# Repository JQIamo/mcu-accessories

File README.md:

# MCU Accessories

Accessory circuits for microcontrollers.

Examples of things to go in this repo: 

* LCD breakout boards
* Breakout boards for Arduino
* Other Arduino shields
* etc...

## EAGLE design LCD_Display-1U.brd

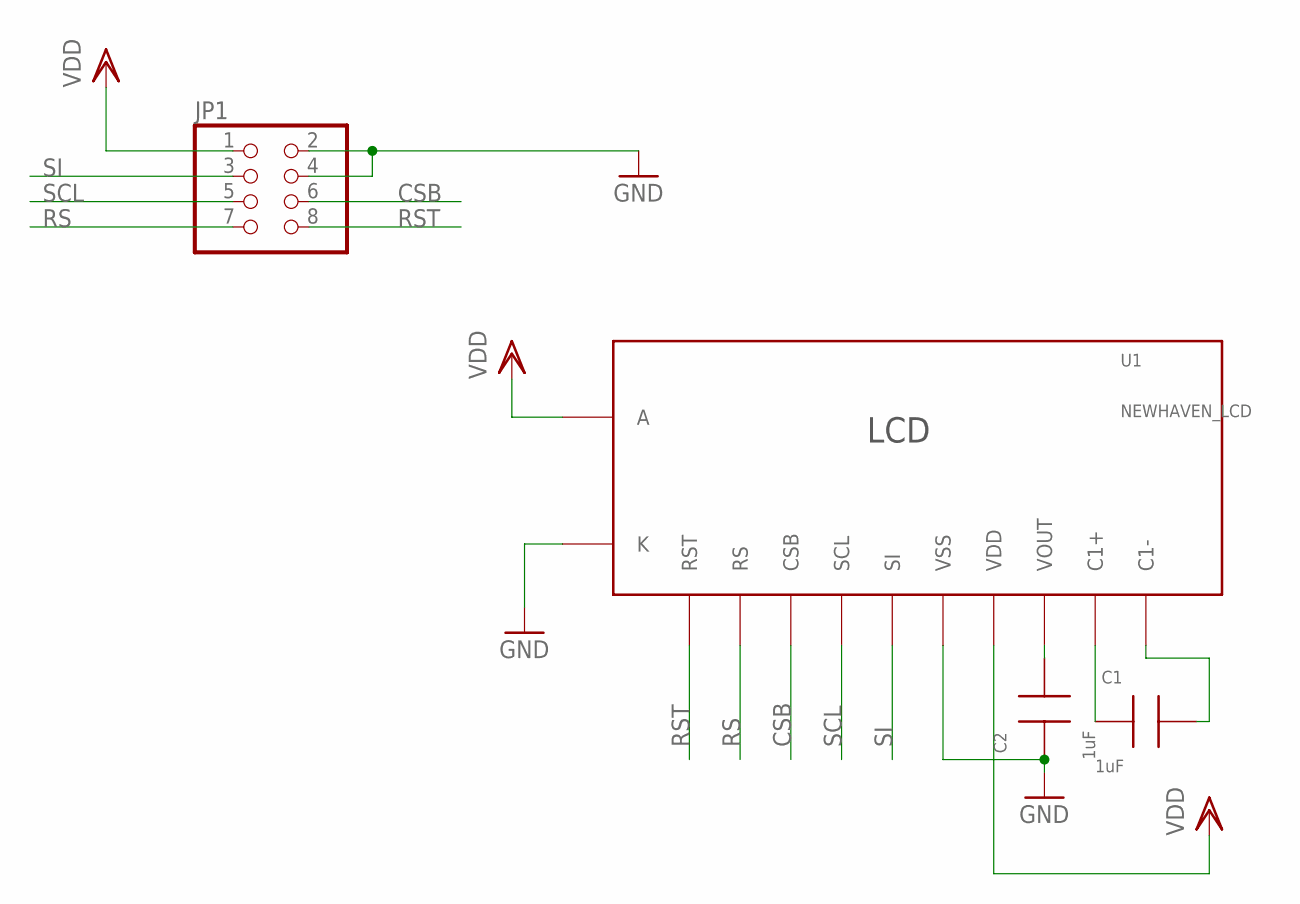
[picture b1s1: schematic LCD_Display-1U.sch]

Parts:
C1, C2: 1uF; 0805; PARTNO CL21A105KBCLNNC
JP1: PINHD-2X4SMT; 2X4SMT; PARTNO 0015912080
U1: NEWHAVEN_LCD; PARTNO NHD-C0216CZ-FSW-FBW-3V3

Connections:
CSB: JP1.6, U1.3 (CSB)
GND: C2.1, JP1.2, JP1.4, U1.6 (VSS), U1.K
unnamed: C1.1, U1.9 (C1+)
unnamed: C1.2, U1.10 (C1-)
unnamed: C2.2, U1.8 (VOUT)
RS: JP1.7, U1.2 (RS)
RST: JP1.8, U1.1 (RST)
SCL: JP1.5, U1.4 (SCL)
SI: JP1.3, U1.5 (SI)
VDD: JP1.1, U1.7 (VDD), U1.A

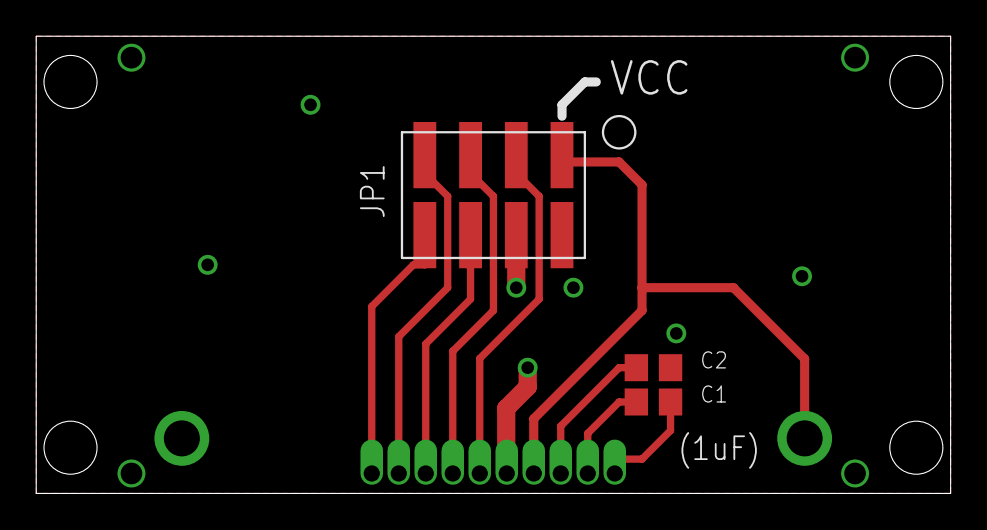
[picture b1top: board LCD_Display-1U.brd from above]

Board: 2 copper layers, 50.8 x 25.4 mm, 4 parts (1 on the bottom side), 10 nets.

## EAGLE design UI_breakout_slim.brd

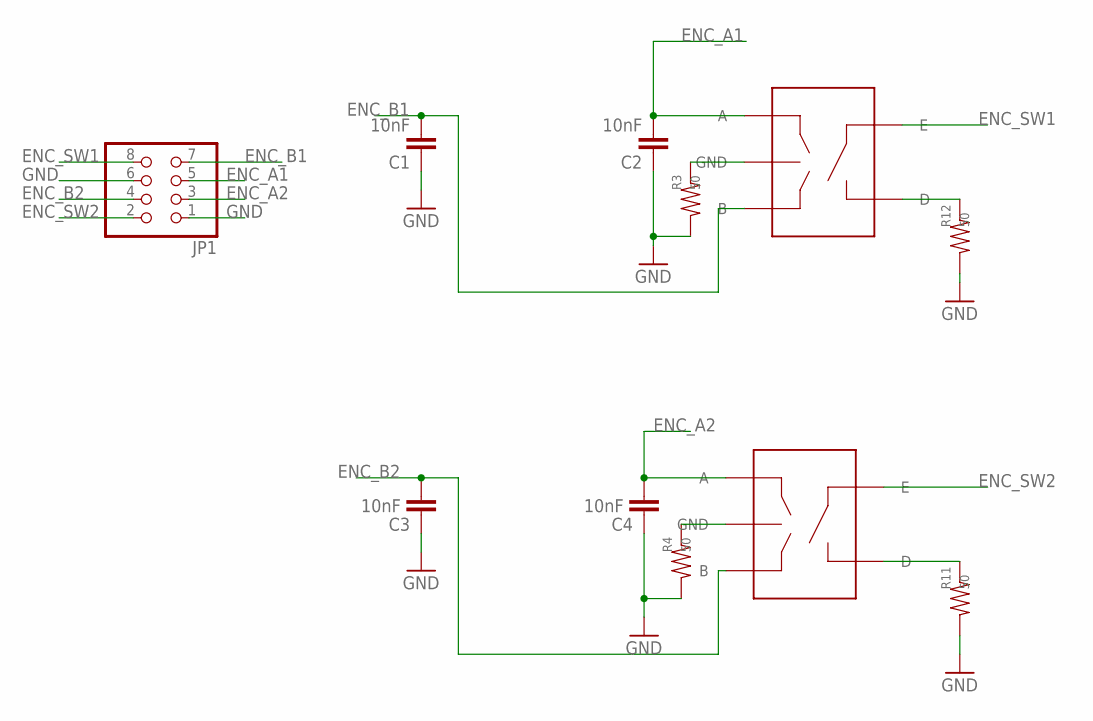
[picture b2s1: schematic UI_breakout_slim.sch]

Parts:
C1, C2, C3, C4: 10nF; C0603
ENC1, ENC2: PEC09; PEC092320FS
JP1: PINHD-2X4-SHROUD; ML08
R3, R4, R11, R12: 50; 0603

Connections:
C: ENC2.C (GND), R4.2
ENC_A1: C2.2, ENC1.A, JP1.5
ENC_A2: C4.2, ENC2.A, JP1.3
ENC_B1: C1.2, ENC1.B, JP1.7
ENC_B2: C3.2, ENC2.B, JP1.4
ENC_SW1: ENC1.E, JP1.8
ENC_SW2: ENC2.E, JP1.2
GND: C1.1, C2.1, C3.1, C4.1, JP1.1, JP1.6, R3.1, R4.1, R11.1, R12.1
unnamed: ENC1.C (GND), R3.2
unnamed: ENC2.D, R11.2
unnamed: ENC1.D, R12.2

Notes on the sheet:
ENC_A2
ENC_B2
ENC_SW2
ENC_SW1
ENC_A1
ENC_B1

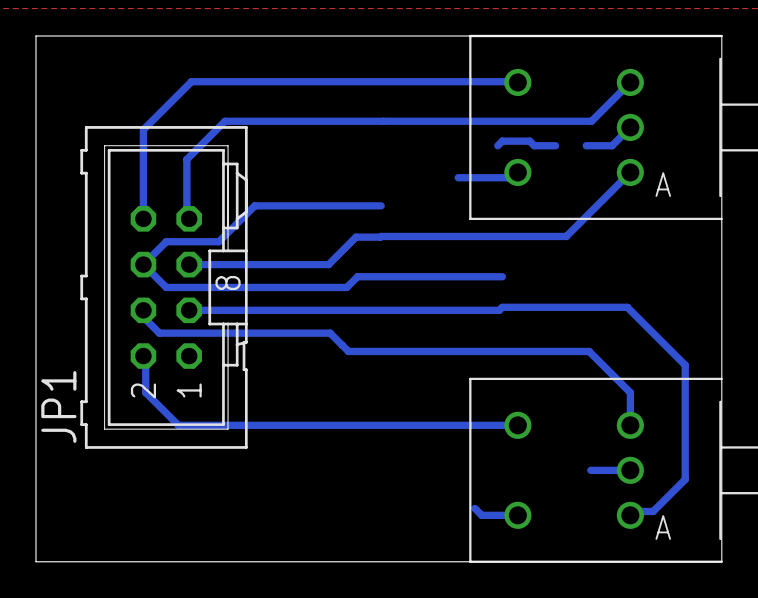
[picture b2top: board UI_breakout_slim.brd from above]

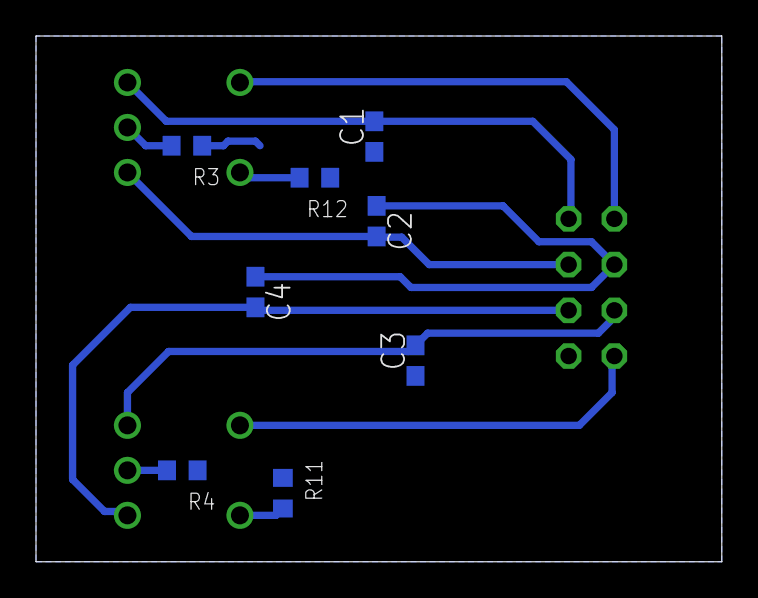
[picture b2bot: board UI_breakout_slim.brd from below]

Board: 2 copper layers, 38.1 x 29.2 mm, 11 parts (8 on the bottom side), 11 nets.

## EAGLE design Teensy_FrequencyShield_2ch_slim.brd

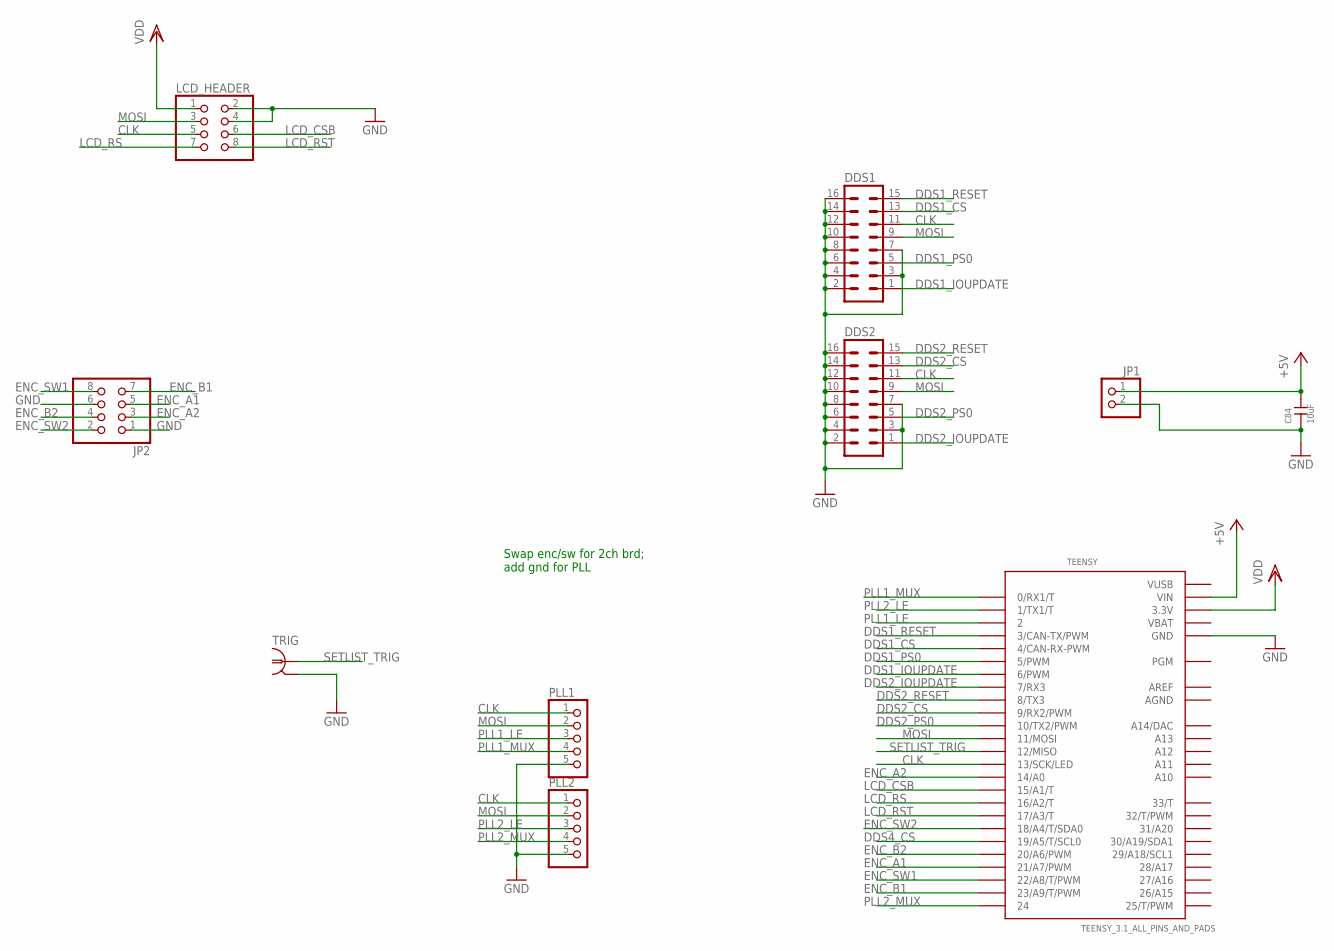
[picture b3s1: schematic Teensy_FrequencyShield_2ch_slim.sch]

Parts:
C84: 10uF; 0805; PARTNO 1276-2890-1-ND
DDS1, DDS2: ML16
JP1: PINHD-1X2; 1X02
JP2: PINHD-2X4-SHROUD; ML08
LCD_HEADER: PINHD-2X4-SHROUD; ML08
PLL1, PLL2: PINHD-1X5; 1X05
TEENSY: TEENSY_3.1_ALL_PINS_AND_PADS; TEENSY_3.1_ALLPINS
TRIG: BNC-H; BNC90

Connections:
+5V: C84.2, JP1.1, TEENSY.VIN
AGND: TEENSY.AGND
AREF: TEENSY.AREF
CLK: DDS1.11, DDS2.11, LCD_HEADER.5, PLL1.1, PLL2.1, TEENSY.13 (13/SCK/LED)
DDS1_CS: DDS1.13, TEENSY.4 (4/CAN-RX-PWM)
DDS1_IOUPDATE: DDS1.1, TEENSY.6 (6/PWM)
DDS1_PS0: DDS1.5, TEENSY.5 (5/PWM)
DDS1_RESET: DDS1.15, TEENSY.3 (3/CAN-TX/PWM)
DDS2_CS: DDS2.13, TEENSY.9 (9/RX2/PWM)
DDS2_IOUPDATE: DDS2.1, TEENSY.7 (7/RX3)
DDS2_PS0: DDS2.5, TEENSY.10 (10/TX2/PWM)
DDS2_RESET: DDS2.15, TEENSY.8 (8/TX3)
DDS4_CS: TEENSY.19/A5 (19/A5/T/SCL0)
ENC_A1: JP2.5, TEENSY.21/A7 (21/A7/PWM)
ENC_A2: JP2.3, TEENSY.14/A0
ENC_B1: JP2.7, TEENSY.23/A9 (23/A9/T/PWM)
ENC_B2: JP2.4, TEENSY.20/A6 (20/A6/PWM)
ENC_SW1: JP2.8, TEENSY.22/A8 (22/A8/T/PWM)
ENC_SW2: JP2.2, TEENSY.18/A4 (18/A4/T/SDA0)
EROU: LCD_HEADER.1, TEENSY.3.3V, TEENSY.3.3V1 (3.3V), TEENSY.3.3V2 (3.3V)
GND: C84.1, DDS1.2, DDS1.3, DDS1.4, DDS1.6, DDS1.7, DDS1.8, DDS1.10, DDS1.12, DDS1.14, DDS1.16, DDS2.2, DDS2.3, DDS2.4, DDS2.6, DDS2.7, DDS2.8, DDS2.10, DDS2.12, DDS2.14, DDS2.16, JP1.2, JP2.1, JP2.6, LCD_HEADER.2, LCD_HEADER.4, PLL1.5, PLL2.5, TEENSY.GND, TEENSY.GND1 (GND), TEENSY.GND2 (GND), TRIG.2
LCD_CSB: LCD_HEADER.6, TEENSY.15/A1 (15/A1/T)
LCD_RS: LCD_HEADER.7, TEENSY.16/A2 (16/A2/T)
LCD_RST: LCD_HEADER.8, TEENSY.17/A3 (17/A3/T)
MOSI: DDS1.9, DDS2.9, LCD_HEADER.3, PLL1.2, PLL2.2, TEENSY.11 (11/MOSI)
PLL1_LE: PLL1.3, TEENSY.2
PLL1_MUX: PLL1.4, TEENSY.0 (0/RX1/T)
PLL2_LE: PLL2.3, TEENSY.1 (1/TX1/T)
PLL2_MUX: PLL2.4, TEENSY.24
SETLIST_TRIG: TEENSY.12 (12/MISO), TRIG.1
VBAT: TEENSY.VBAT
VUSB: TEENSY.VUSB

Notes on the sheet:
Swap enc/sw for 2ch brd; add gnd for PLL

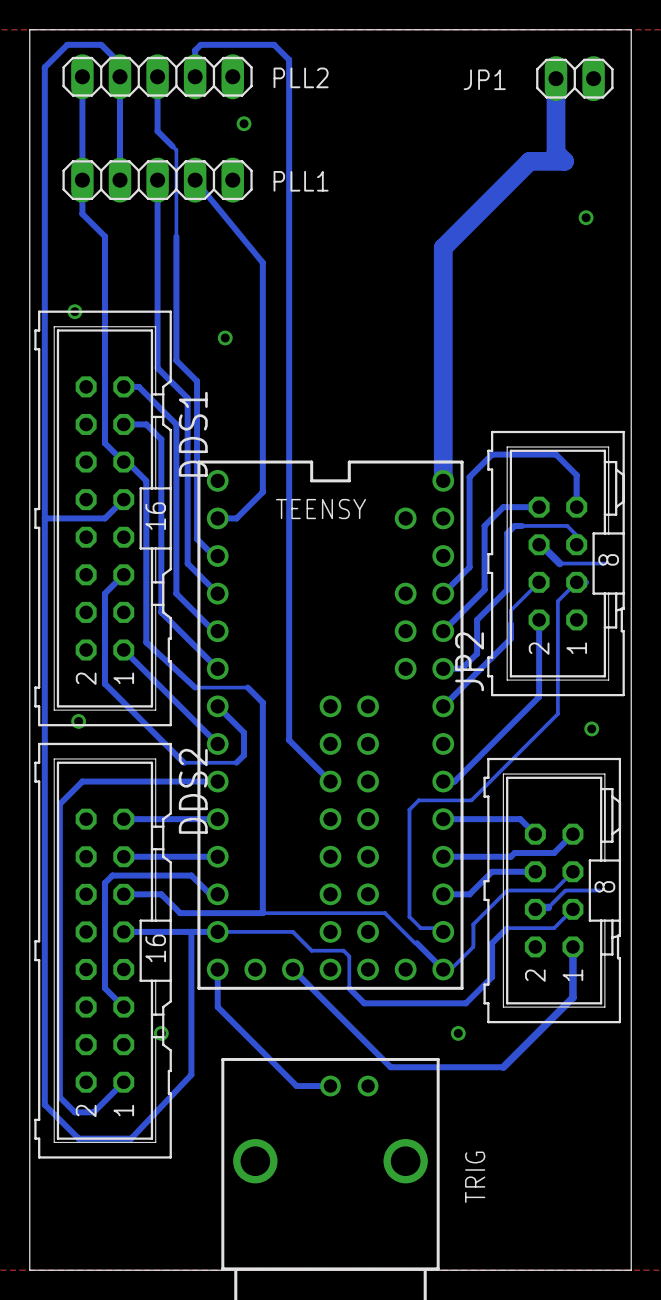
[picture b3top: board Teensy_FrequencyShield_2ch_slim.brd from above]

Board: 2 copper layers, 40.6 x 83.8 mm, 10 parts (1 on the bottom side), 27 nets.

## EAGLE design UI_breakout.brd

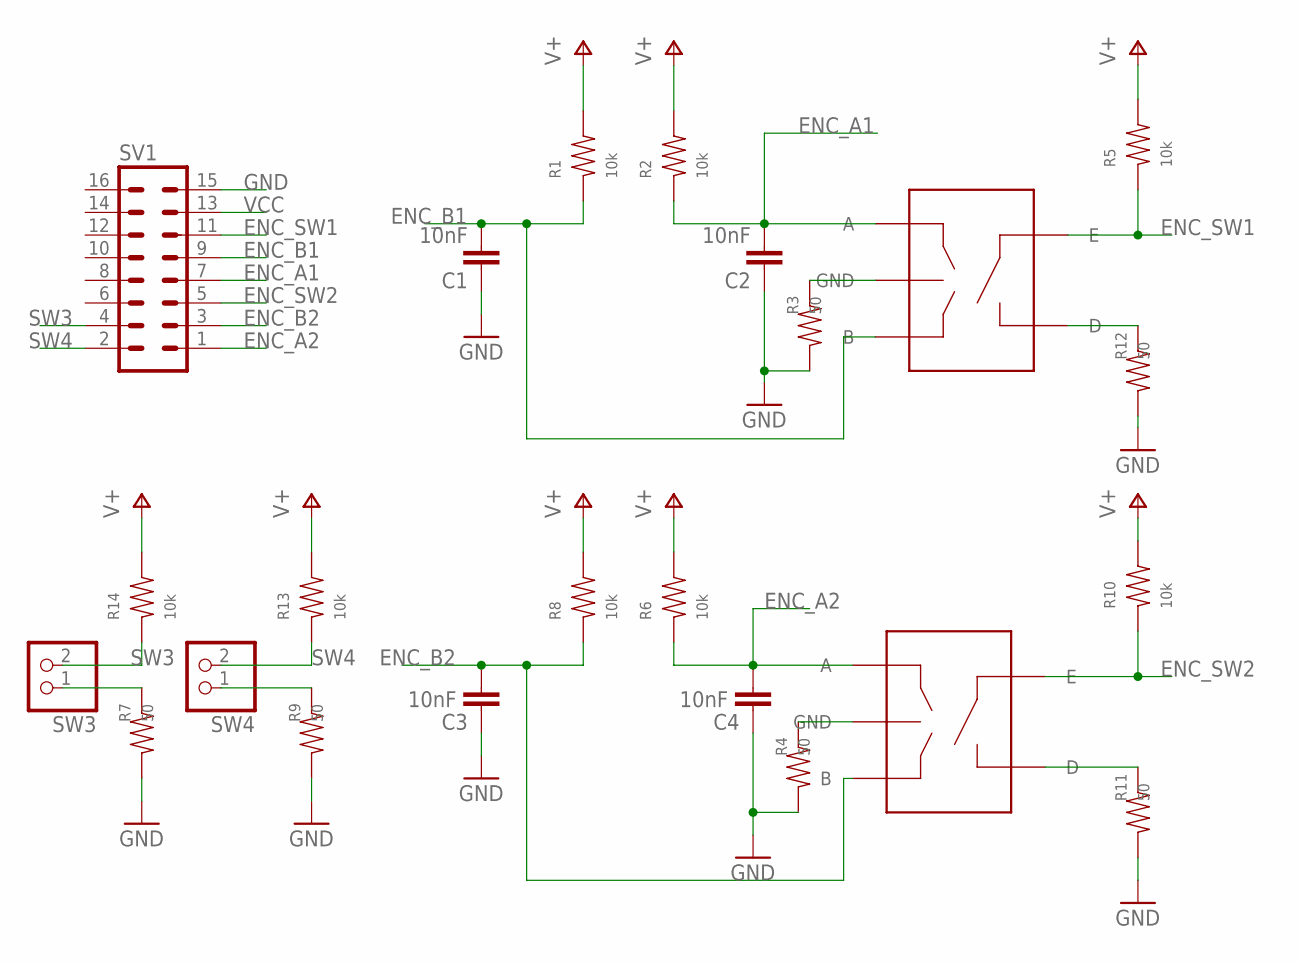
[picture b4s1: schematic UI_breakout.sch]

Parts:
C1, C2, C3, C4: 10nF; C0603
ENC1, ENC2: PEC09; PEC092320FS
R1, R2, R5, R6, R8, R10, R13, R14: 10k; 0603
R3, R4, R7, R9, R11, R12: 50; 0603
SV1: ML16
SW3, SW4: PINHD-1X2; 1X02

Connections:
C: ENC2.C (GND), R4.2
ENC_A1: C2.2, ENC1.A, R2.1, SV1.7
ENC_A2: C4.2, ENC2.A, R6.1, SV1.1
ENC_B1: C1.2, ENC1.B, R1.1, SV1.9
ENC_B2: C3.2, ENC2.B, R8.1, SV1.3
ENC_SW1: ENC1.E, R5.1, SV1.11
ENC_SW2: ENC2.E, R10.1, SV1.5
GND: C1.1, C2.1, C3.1, C4.1, R3.1, R4.1, R7.1, R9.1, R11.1, R12.1, SV1.15
unnamed: R7.2, SW3.1
unnamed: R9.2, SW4.1
unnamed: ENC1.C (GND), R3.2
unnamed: ENC2.D, R11.2
unnamed: ENC1.D, R12.2
SW3: R14.1, SV1.4, SW3.2
SW4: R13.1, SV1.2, SW4.2
VCC: R1.2, R2.2, R5.2, R6.2, R8.2, R10.2, R13.2, R14.2, SV1.13

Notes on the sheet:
ENC_A2
ENC_B2
ENC_SW2
ENC_SW1
ENC_A1
ENC_B1

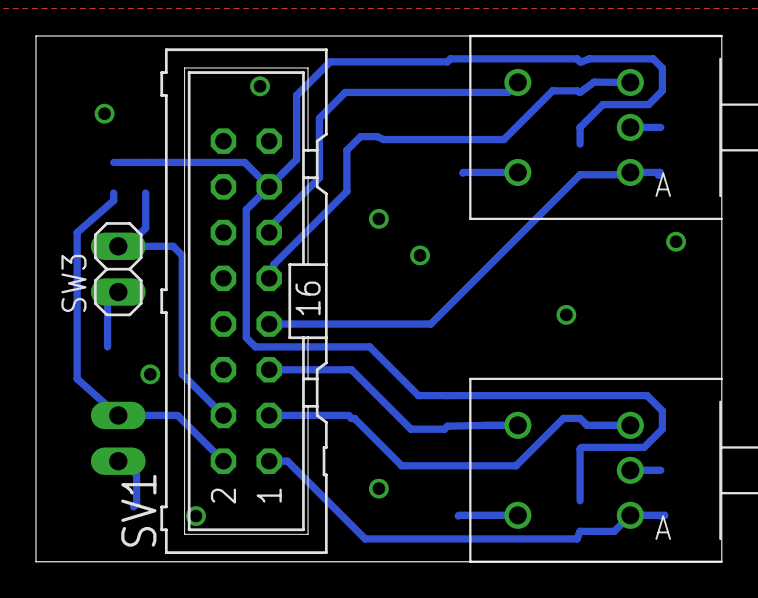
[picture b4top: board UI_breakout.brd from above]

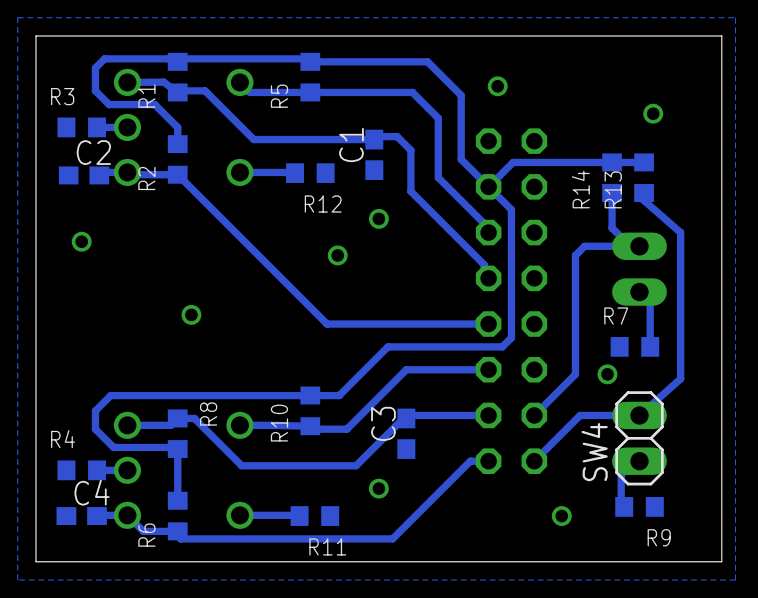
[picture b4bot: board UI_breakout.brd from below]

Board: 2 copper layers, 38.1 x 29.2 mm, 23 parts (19 on the bottom side), 16 nets.

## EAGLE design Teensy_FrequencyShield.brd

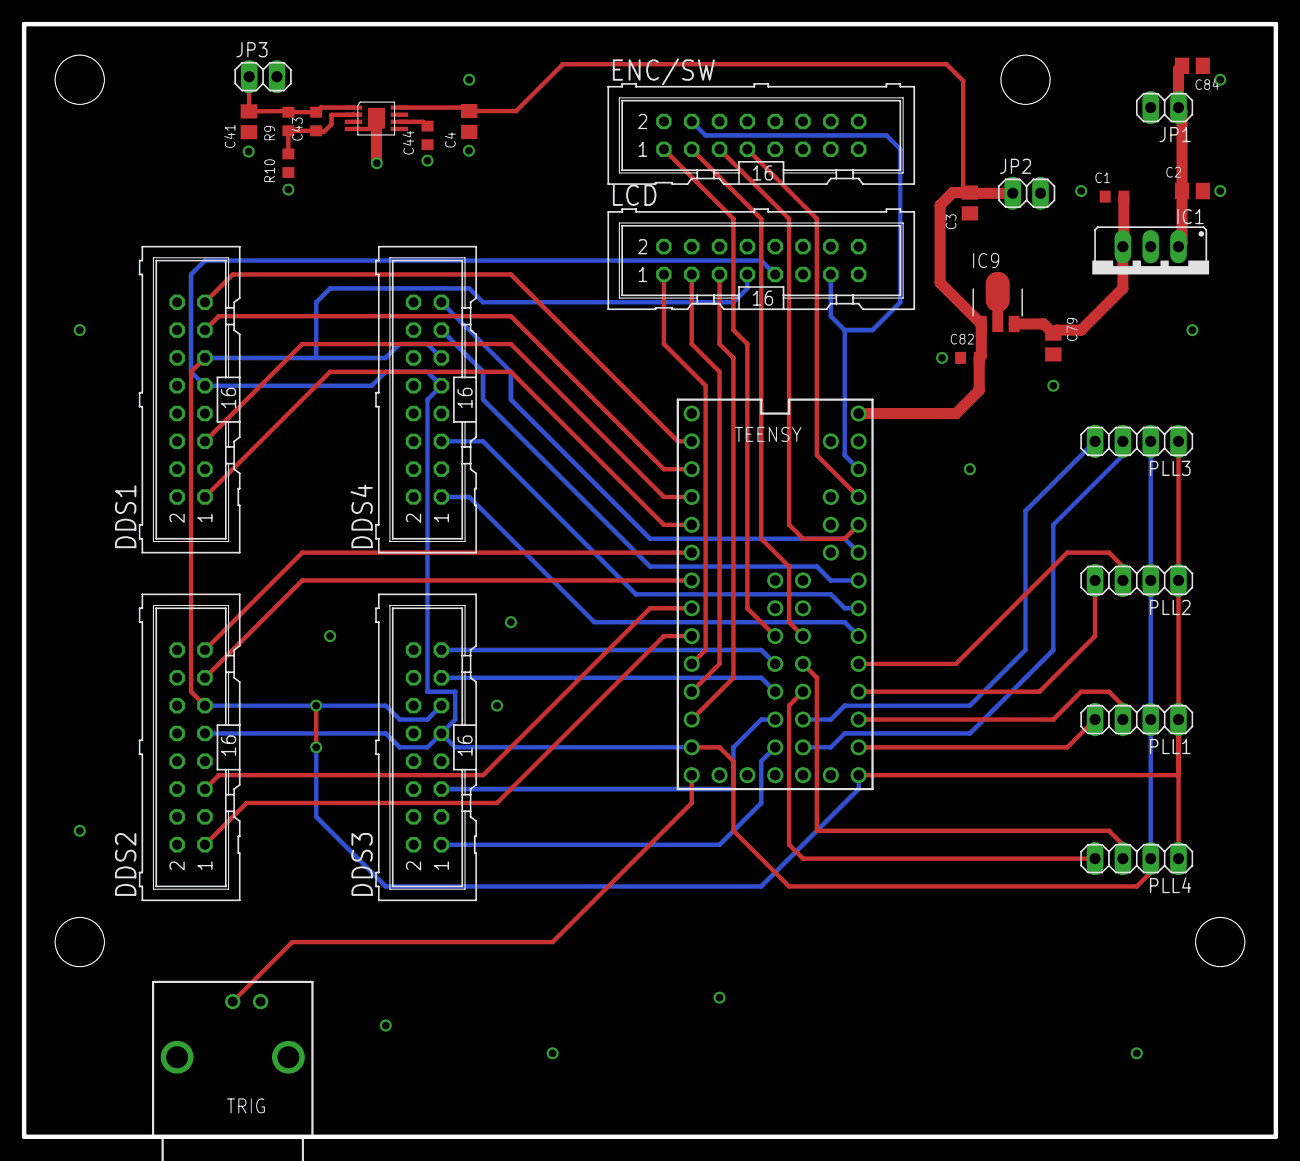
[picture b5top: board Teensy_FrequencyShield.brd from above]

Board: 2 copper layers, 114.3 x 101.6 mm, 30 parts (0 on the bottom side), 42 nets.

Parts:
C1, C82: 100nF; 0603
C2, C79: 1uF; 0805
C3, C4, C41, C84: 10uF; 0805
C43, C44: 10nF; 0603
DDS1, DDS2, DDS3, DDS4: ML16
ENC/SW: ML16
IC1: TO220
IC9: 78L05F; SOT89
JP1, JP2, JP3: 1X02
LCD: ML16
PLL1, PLL2, PLL3, PLL4: 1X04
R9, R10: 0603
TEENSY: TEENSY_3.1_ALL_PINS_AND_PADS; TEENSY_3.1_ALLPINS
TRIG: BNC-H; BNC90
U4: TPS7A4901; DGN

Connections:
+5V: C3.2, C4.2, C82.2, IC9.1, JP2.1, TEENSY.VIN, U4.IN
CLK: DDS1.11, DDS2.11, DDS3.11, DDS4.11, LCD.7, PLL1.1, PLL2.1, PLL3.1, PLL4.1, TEENSY.13
DDS1_CS: DDS1.13, TEENSY.1
DDS1_IOUPDATE: DDS1.1, TEENSY.3
DDS1_PS0: DDS1.5, TEENSY.2
DDS1_RESET: DDS1.15, TEENSY.0
DDS2_CS: DDS2.13, TEENSY.5
DDS2_IOUPDATE: DDS2.1, TEENSY.7
DDS2_PS0: DDS2.5, TEENSY.6
DDS2_RESET: DDS2.15, TEENSY.4
DDS3_CS: DDS3.13, TEENSY.26
DDS3_IOUPDATE: DDS3.1, TEENSY.28
DDS3_PS0: DDS3.5, TEENSY.27
DDS3_RESET: DDS3.15, TEENSY.25
DDS4_CS: DDS4.13, TEENSY.20/A6
DDS4_IOUPDATE: DDS4.1, TEENSY.18/A4
DDS4_PS0: DDS4.5, TEENSY.19/A5
DDS4_RESET: DDS4.15, TEENSY.21/A7
ENC_A: ENC/SW.7, TEENSY.23/A9
ENC_B: ENC/SW.5, TEENSY.22/A8
ENC_SW: ENC/SW.1, TEENSY.24
GND: C1.1, C2.2, C3.1, C4.1, C41.1, C44.1, C79.2, C82.1, C84.1, DDS1.2, DDS1.3, DDS1.4, DDS1.6, DDS1.7, DDS1.8, DDS1.10, DDS1.12, DDS1.14, DDS1.16, DDS2.2, DDS2.3, DDS2.4, DDS2.6, DDS2.7, DDS2.8, DDS2.10, DDS2.12, DDS2.14, DDS2.16, DDS3.2, DDS3.3, DDS3.4, DDS3.6, DDS3.7, DDS3.8, DDS3.10, DDS3.12, DDS3.14, DDS3.16, DDS4.2, DDS4.3, DDS4.4, DDS4.6, DDS4.7, DDS4.8, DDS4.10, DDS4.12, DDS4.14, DDS4.16, ENC/SW.15, IC1.2, IC9.2, IC9.2@1, JP1.2, JP2.2, JP3.2, LCD.11, R10.1, TEENSY.AGND, TEENSY.GND, TEENSY.GND1, TEENSY.GND2, TRIG.2, U4.GND, U4.GND1
LCD_CSB: LCD.5, TEENSY.10
LCD_RS: LCD.3, TEENSY.9
LCD_RST: LCD.1, TEENSY.8
MOSI: DDS1.9, DDS2.9, DDS3.9, DDS4.9, LCD.9, PLL1.2, PLL2.2, PLL3.2, PLL4.2, TEENSY.11
unnamed: C41.2, C43.2, JP3.1, R9.2, U4.OUT
unnamed: C1.2, C79.1, IC1.3, IC9.3
unnamed: C43.1, R9.1, R10.2, U4.FB
unnamed: C44.2, U4.NR/SS
PLL1_LE: PLL1.3, TEENSY.15/A1
PLL1_MUX: PLL1.4, TEENSY.14/A0
PLL2_LE: PLL2.3, TEENSY.17/A3
PLL2_MUX: PLL2.4, TEENSY.16/A2
PLL3_LE: PLL3.3, TEENSY.29
PLL3_MUX: PLL3.4, TEENSY.30
PLL4_LE: PLL4.3, TEENSY.32
PLL4_MUX: PLL4.4, TEENSY.31
SETLIST_TRIG: TEENSY.12, TRIG.1
SW1: ENC/SW.3, TEENSY.33
V+: C2.1, C84.2, IC1.1, JP1.1
VDD: ENC/SW.4, LCD.13, TEENSY.3.3V, TEENSY.3.3V1, TEENSY.3.3V2

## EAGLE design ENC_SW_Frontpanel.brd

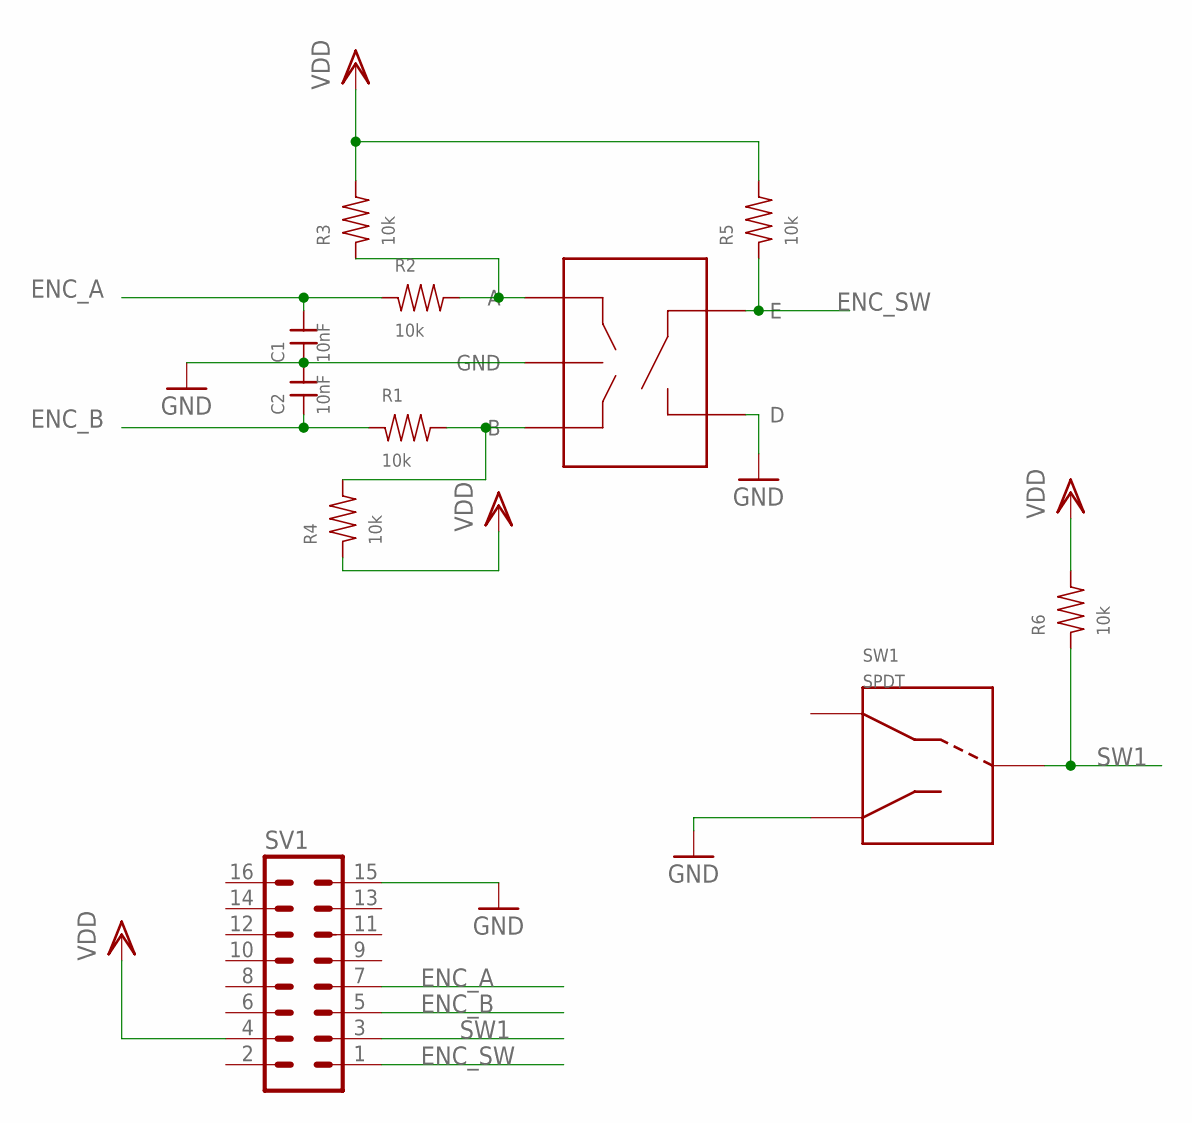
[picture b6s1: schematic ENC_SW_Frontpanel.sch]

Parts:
C1, C2: 10nF; 0603
ENC1: PEC09; PEC092320FS; PARTNO PEC09-2320F-S0015-ND
R1, R2, R3, R4, R5, R6: 10k; 0603
SV1: ML16
SW1: SPDT; 100SP1-M7

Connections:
ENC_A: C1.2, R2.1, SV1.7
ENC_B: C2.1, R1.1, SV1.5
ENC_SW: ENC1.E, R5.1, SV1.1
GND: C1.1, C2.2, ENC1.C (GND), ENC1.D, SV1.15, SW1.IN2
unnamed: ENC1.B, R1.2, R4.2
unnamed: ENC1.A, R2.2, R3.1
SW1: R6.1, SV1.3, SW1.OUT
VDD: R3.2, R4.1, R5.2, R6.2, SV1.4

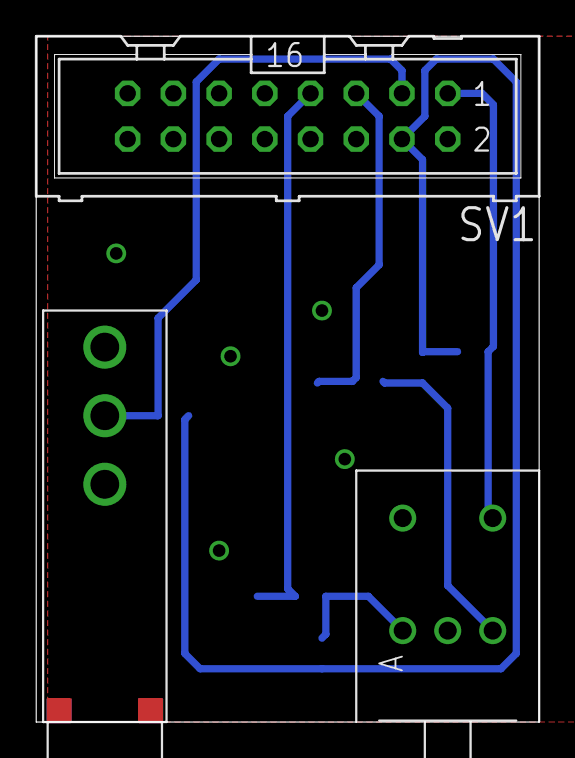
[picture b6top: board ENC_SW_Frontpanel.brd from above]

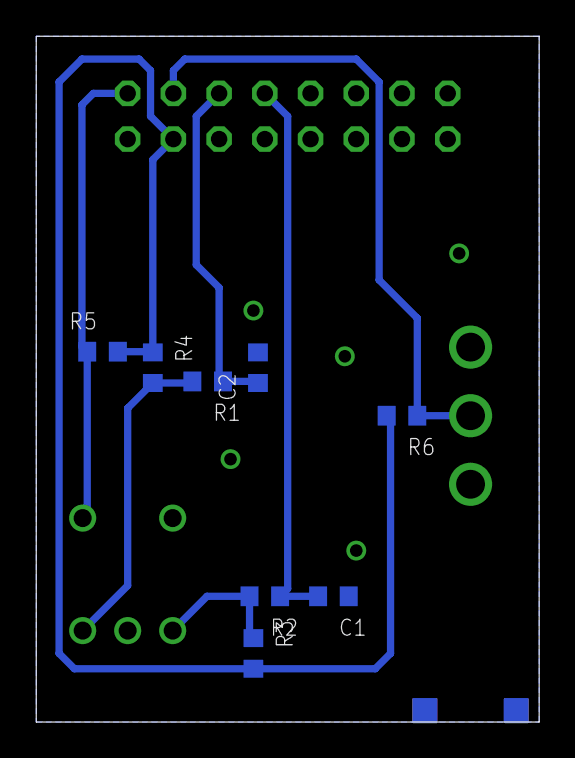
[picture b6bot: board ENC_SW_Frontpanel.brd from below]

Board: 2 copper layers, 27.9 x 38.1 mm, 11 parts (8 on the bottom side), 8 nets.

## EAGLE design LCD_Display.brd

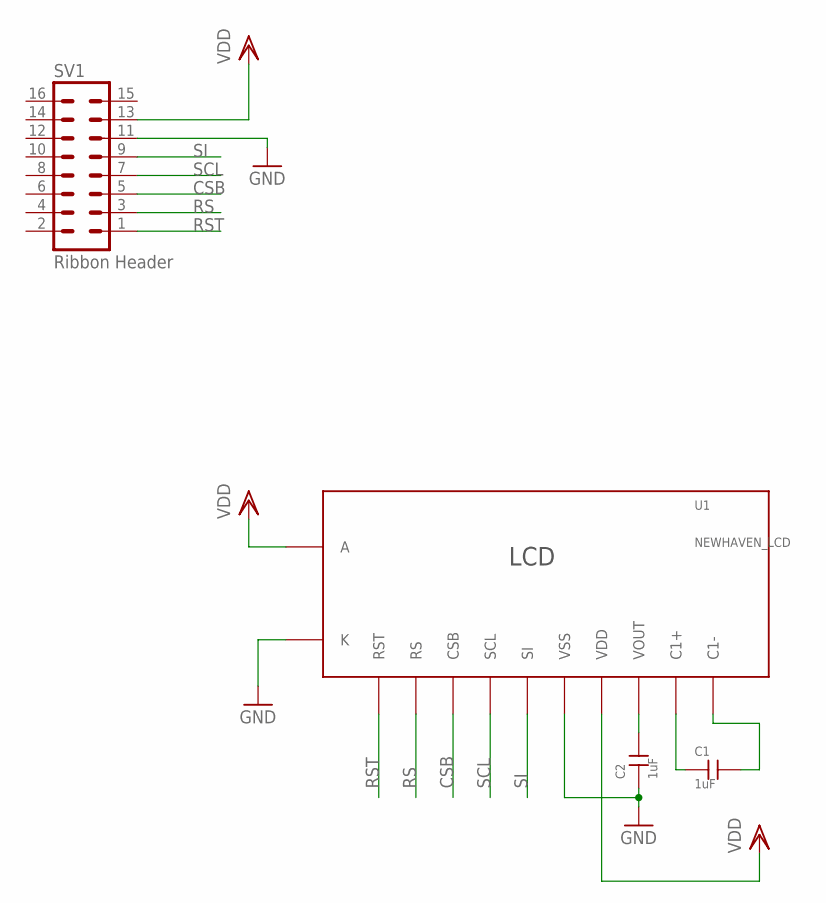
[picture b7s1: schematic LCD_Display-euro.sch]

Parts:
C1, C2: 1uF; 0805; PARTNO 1276-2396-1-ND
SV1: Ribbon Header; ML16; PARTNO S9171-ND
U1: NEWHAVEN_LCD

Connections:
CSB: SV1.5, U1.3 (CSB)
GND: C2.1, SV1.11, U1.6 (VSS), U1.K
unnamed: C1.1, U1.9 (C1+)
unnamed: C1.2, U1.10 (C1-)
unnamed: C2.2, U1.8 (VOUT)
RS: SV1.3, U1.2 (RS)
RST: SV1.1, U1.1 (RST)
SCL: SV1.7, U1.4 (SCL)
SI: SV1.9, U1.5 (SI)
VDD: SV1.13, U1.7 (VDD), U1.A

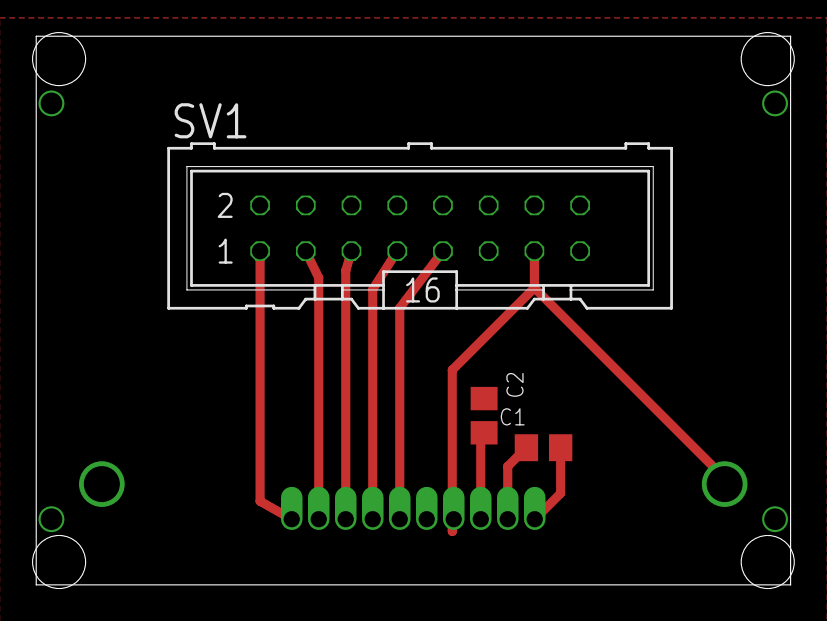
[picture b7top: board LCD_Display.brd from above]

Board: 2 copper layers, 41.9 x 30.5 mm, 4 parts (1 on the bottom side), 10 nets.

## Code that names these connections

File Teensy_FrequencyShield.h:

/*
   Teensy_FrequencyShield.h  - Pin mappings for the Teensy_FrequencyShield
   
   Created by Neal Pisenti, 2015
   JQI - Joint Quantum Institute

   This program is free software: you can redistribute it and/or modify
   it under the terms of the GNU General Public License as published by
   the Free Software Foundation, either version 3 of the License, or
   (at your option) any later version.

   This program is distributed in the hope that it will be useful,
   but WITHOUT ANY WARRANTY; without even the implied warranty of
   MERCHANTABILITY or FITNESS FOR A PARTICULAR PURPOSE.  See the
   GNU General Public License for more details.

   You should have received a copy of the GNU General Public License
   along with this program.  If not, see <http://www.gnu.org/licenses/>.

*/

/*!	\file	Teensy_FrequencyShield.h
 *	\brief	Pin mappings for Teensy_FrequencyShield PCB.
 *	\details Define statements for pin mappings on Teensy frequency shield.
 *          See https://github.com/JQIamo/mcu-accessories for the breakout
 *          shield, and https://www.pjrc.com/teensy/teensy31.html for info
 *			on the Teensy dev board.
 *
 *	\author	Neal Pisenti <npisenti@umd.edu>
 *  \version 0.1
 *	\date	2015-02-28
 */


/*! \name Pins for DDS-type objects
 *
 */
//! @{

#define DDS1_RESET 		0
#define DDS1_CS 		1
#define DDS1_PS0 		2
#define DDS1_IOUPDATE 	3

#define DDS2_RESET 		4
#define DDS2_CS 		5
#define DDS2_PS0 		6
#define DDS2_IOUPDATE 	7

#define DDS3_RESET 		25
#define DDS3_CS 		26
#define DDS3_PS0 		27
#define DDS3_IOUPDATE 	28

#define DDS4_RESET		21
#define DDS4_CS			20
#define DDS4_PS0		19
#define DDS4_IOUPDATE	18

//! @}

/*! \name Pins for PLL-type objects
 *
 */
//! @{
#define PLL1_MUX		A0
#define PLL1_MUX_D		14
#define PLL1_LE			15

#define PLL2_MUX		A2
#define PLL2_MUX_D		16
#define PLL2_LE			17

#define PLL3_MUX		A19
#define PLL3_MUX_D		30
#define PLL3_LE			29

#define PLL4_MUX		A20
#define PLL4_MUX_D		31
#define PLL4_LE			32

//!@}

/*! \name Pins for LCD & Switches/encoders
 *
 */
//! @{

#define LCD_RST			8
#define LCD_RS			9
#define LCD_CSB			10

#define ENC_A			23
#define ENC_B			22
#define ENC_SW			24

#define SW1				33

//! @}

/*! \name Pins for SPI & SetList triggering
 *
 */
//! @{

#define TEENSY_MOSI		11
#define SETLIST_TRIG	12
#define TEENSY_CLK		13

//! @}

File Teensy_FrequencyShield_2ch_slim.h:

/*
   Teensy_FrequencyShield_2ch.h  - Pin mappings for Teensy_FrequencyShield_2ch
   
   Created by Neal Pisenti, 2015
   JQI - Joint Quantum Institute

   This program is free software: you can redistribute it and/or modify
   it under the terms of the GNU General Public License as published by
   the Free Software Foundation, either version 3 of the License, or
   (at your option) any later version.

   This program is distributed in the hope that it will be useful,
   but WITHOUT ANY WARRANTY; without even the implied warranty of
   MERCHANTABILITY or FITNESS FOR A PARTICULAR PURPOSE.  See the
   GNU General Public License for more details.

   You should have received a copy of the GNU General Public License
   along with this program.  If not, see <http://www.gnu.org/licenses/>.

*/

/*!	\file	Teensy_FrequencyShield.h
 *	\brief	Pin mappings for Teensy_FrequencyShield PCB.
 *	\details Define statements for pin mappings on Teensy frequency shield.
 *          See https://github.com/JQIamo/mcu-accessories for the breakout
 *          shield, and https://www.pjrc.com/teensy/teensy31.html for info
 *			on the Teensy dev board.
 *
 *	\author	Neal Pisenti <npisenti@umd.edu>
 *  \version 0.1
 *	\date	2015-02-28
 */


/*! \name Pins for DDS-type objects
 *
 */
//! @{

#define DDS1_RESET 		3
#define DDS1_CS 		4
#define DDS1_PS0 		5
#define DDS1_IOUPDATE 	6

#define DDS2_RESET 		8
#define DDS2_CS 		9
#define DDS2_PS0 		10
#define DDS2_IOUPDATE 	7

//! @}

/*! \name Pins for PLL-type objects
 
 Use PLL1_MUX_D for digital inputs, and PLL1_MUX for analog inputs.
 
 */
//! @{
//#define PLL1_MUX		0
#define PLL1_MUX_D		0
#define PLL1_LE			2

//#define PLL2_MUX		A4
#define PLL2_MUX_D		24
#define PLL2_LE			1

//!@}

/*! \name Pins for LCD & Switches/encoders
 *
 */
//! @{

#define LCD_RST			17
#define LCD_RS			16
#define LCD_CSB			15

#define ENC_A2			21
#define ENC_B2			23
#define ENC_SW2			22

#define ENC_A1			14
#define ENC_B1			20
#define ENC_SW1			18

//! @}

/*! \name Pins for SPI & SetList triggering
 *
 */
//! @{

//#define MOSI			11
#define SETLIST_TRIG	12
//#define CLK				13

//! @}

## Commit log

2015-02-02 Initial commit; description of repository
2015-02-02 Added readme file
2015-02-24 Basic schematic + layout for LCD board
2015-02-25 Added Teensy packages
2015-02-25 Added Teensy devices
    Accidentally added just package footprints in previous commit;
    now teensy device is in library as well.
2015-02-25 Initial commit Teensy_FrequencyShield
    Planning to implement:
    * 4x "basic" DDS boards
    * 4x "basic" PLL boards
    * Display + rotary encoder
    * Trigger input for SetListArduino
2015-02-27 teensy board with two dds channels and 2 plls
2015-02-28 Tweaked pin layout; added back in extra DDS & PLL channel names to Teensy pinout
2015-02-28 Gerbers for Teensy_FrequencyShield_2ch
2015-02-28 Added C/C++ header file defining pinouts for the TeensyFrequencyShield
2015-02-28 Added dimensions, tidied up
2015-02-28 Renamed LCD_Display to LCD_Display-euro
    Sized for 12HP eurocard module
2015-02-28 Tweaked hole spacing; exported gerbers for LCD_Display Euro
    Sized for 12HP Eurocard module
2015-02-28 Modified LCD board for a 1U budbox rackmounted frontpanel.
2015-02-28 Added SPDT switch
2015-02-28 Added frontpanel breakout board for switch + rotary encoder.
2015-02-28 Added gerbers for ENC_SW_Frontpanel
2015-03-11 Re-routed Teensy_FreqShield to be a (mostly) 1-layer board
    * Easier printing on LKPF machine
    * GND connected through a few rivets to the top layer
2015-03-11 Re-routed several mcu-accessory boards to be (mostly) single-layer
    Will make printing easier on LKPF machine.
2015-03-12 Modified header for new pinout
    * Modified TeensyFrequencyShield_2ch to reflect new pinout
2015-03-30 Enlarged holes for switch; redid SW-ENC-Frontpanel
    Now switch and rotary encoder are 0.75" separated.
2015-04-17 Added WIZNET eval board part
2015-04-18 Added general purpose daughter board header
2015-04-28 Routed generic frequency breakout shield for teensy
2015-04-30 Added optional adjustable Vreg, in case need other voltage.
2015-05-04 Updated pinout for teensy frequency shield
2015-06-23 stashing these here; unsure if i want to keep
2015-07-13 Modified LCD-1U for production run; added 8 pin ribbon connector
2015-07-13 Fixed up Eurocard LCD module for production run
2015-07-13 Updated 8 pin ribbon header silkscreen label
2015-09-15 Added UI_breakout: 2 Encoder + 2 switch
    Schematic taken from UI_breakout.sch from the aom_driver repository. The
    board layout was redone to be all on one side and to have a slightly
    smaller footprint.
2015-09-15 Made the Teensy_FrequencyShield_2ch slimmer
    The board is very slightly narrower now, (1.6" instead of 1.8"). Still
    to update on this board: LCD connector to 8 pin ribbon instead of 16
    pin. Add gnd pin to PLL headers.
2016-01-30 Added Wurth EMI shield
2016-01-30 Updated 2ch teensy frequency breakout
    * uses 8-pin LCD and encoder headers
    * other changes possible...
2016-01-30 Miscellaneous circuits of varying completeness
2017-02-04 Rotated connector on LCD display for eurocard
    I believe it should still be rotated 180 degrees to match IDC cable
    orientation better.
2018-05-16 MacroFab Files
    Added files to use Macrofab to get PCBs.
    DSB
